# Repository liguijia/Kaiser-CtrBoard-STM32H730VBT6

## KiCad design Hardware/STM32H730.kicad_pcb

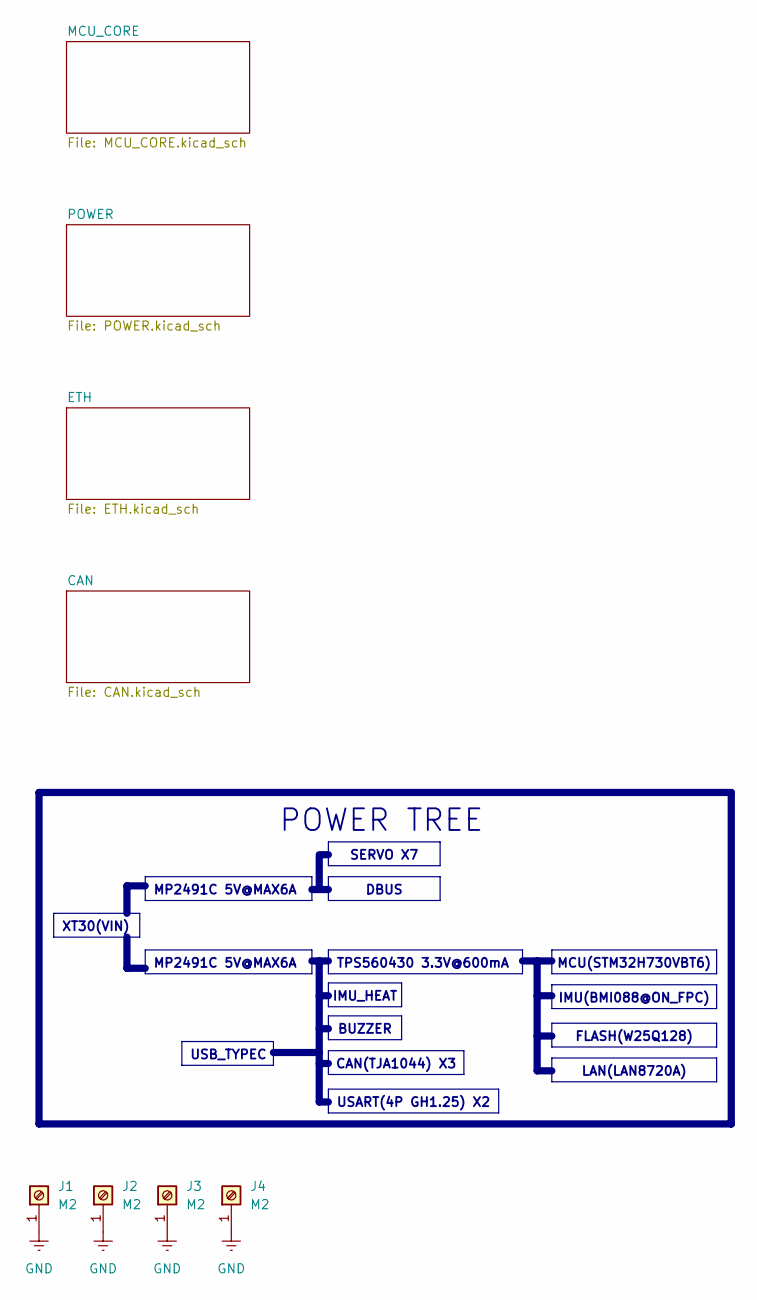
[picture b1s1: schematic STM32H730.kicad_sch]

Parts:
J1, J2, J3, J4: M2; MountingHole_2.2mm_M2_DIN965_Pad

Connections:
GND: J1.1, J2.1, J3.1, J4.1; also elsewhere on the board

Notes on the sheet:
LAN(LAN8720A)
SERVO X7
XT30(VIN)
FLASH(W25Q128)
MCU(STM32H730VBT6)
IMU(BMI088@ON_FPC)
DBUS
IMU_HEAT
CAN(TJA1044) X3
BUZZER
USART(4P GH1.25) X2
TPS560430 3.3V@600mA
MP2491C 5V@MAX6A
USB_TYPEC
POWER TREE

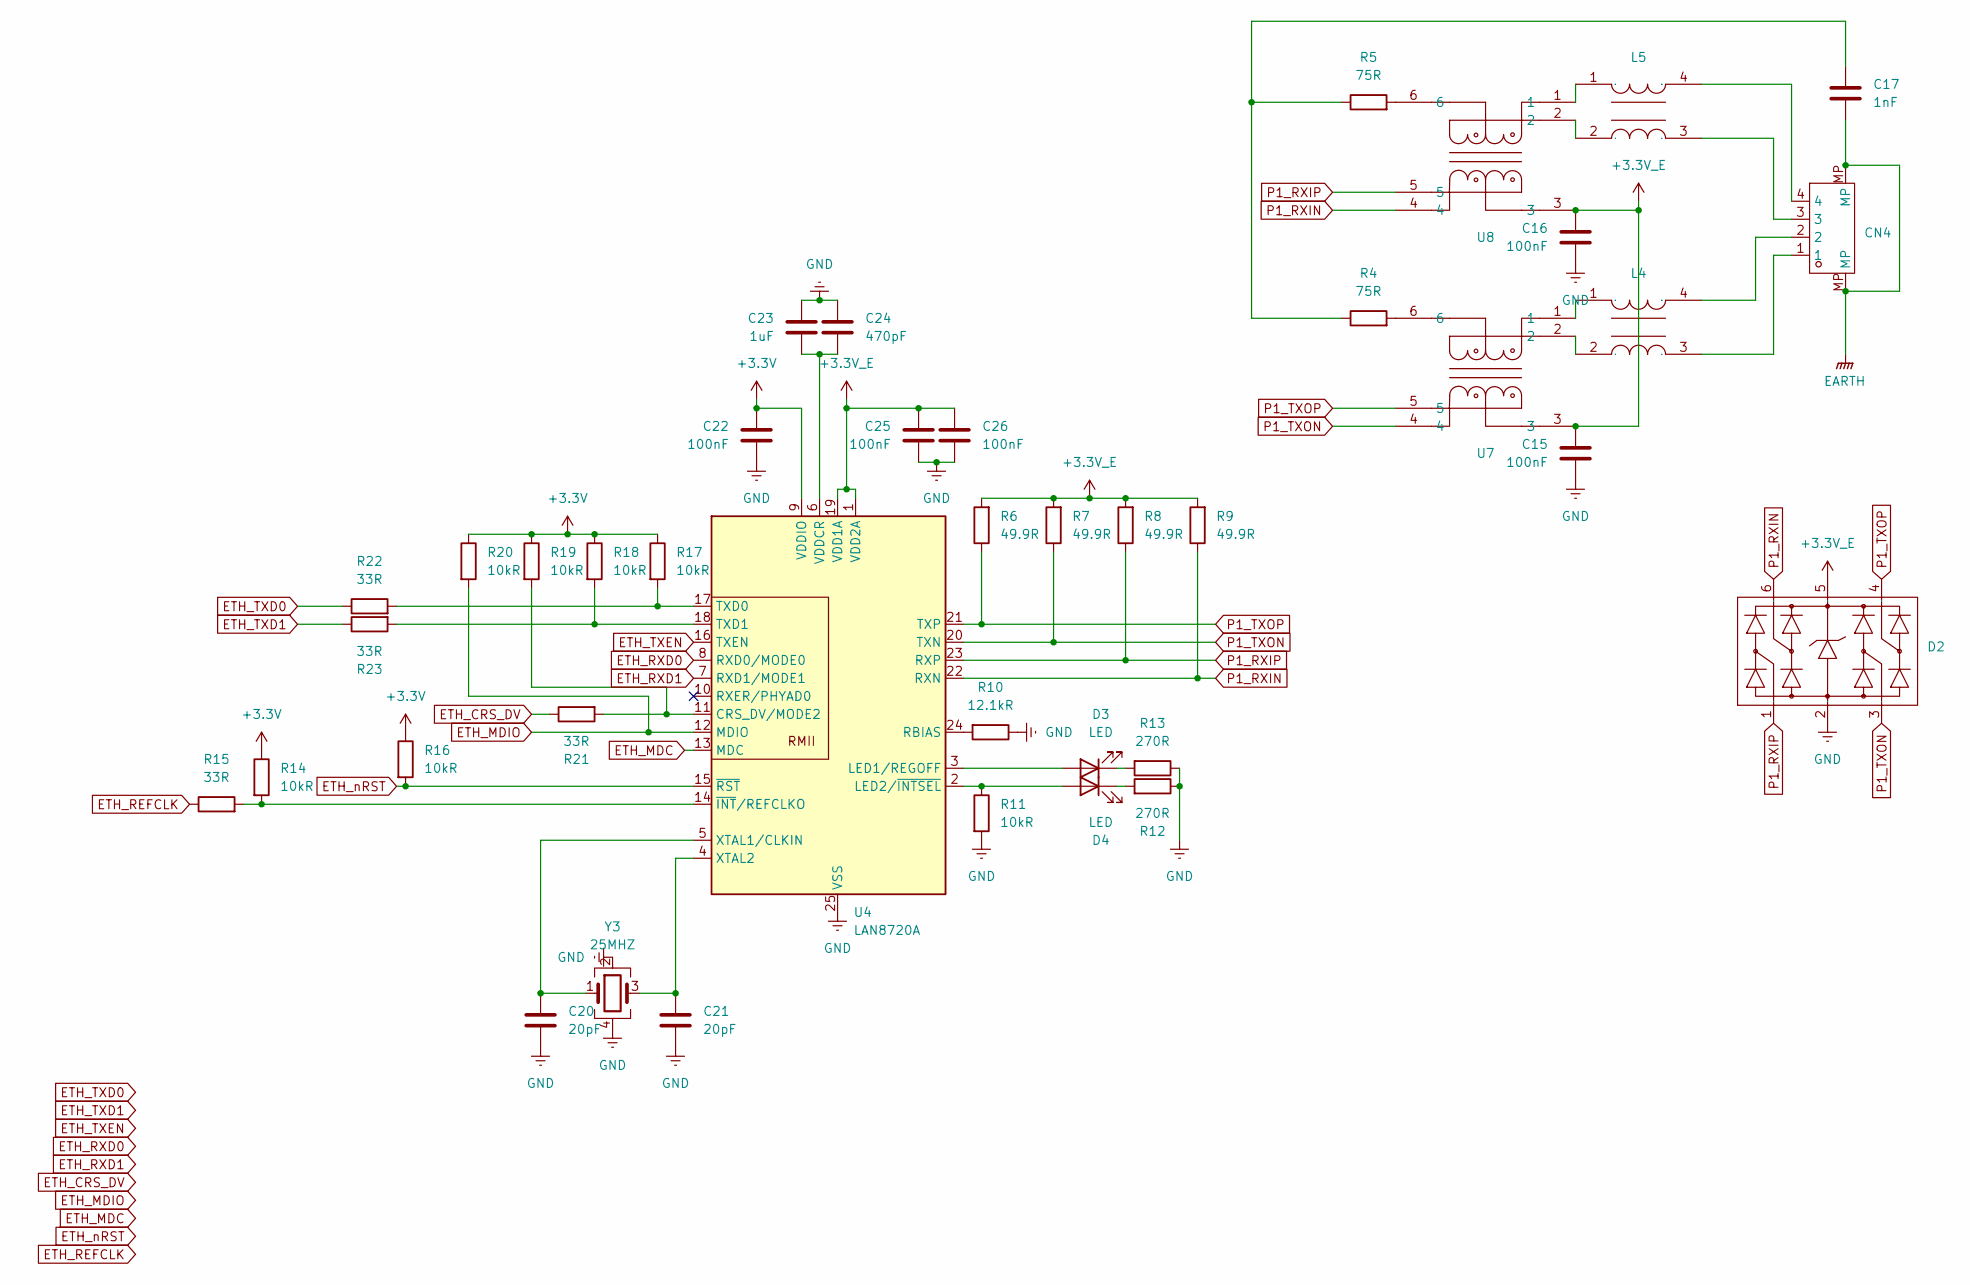
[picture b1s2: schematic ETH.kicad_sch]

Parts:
C15, C16, C22, C25, C26: 100nF; C_0402_1005Metric
C17: 1nF; C_0402_1005Metric
C20, C21: 20pF; C_0402_1005Metric
C23: 1uF; C_0402_1005Metric
C24: 470pF; C_0402_1005Metric
CN4: JST_GH_SM04B-GHS-TB_1x04-1MP_P1.25mm_Horizontal
D2: SOT-23-6_L2.9-W1.6-P0.95-LS2.8-BL
D3, D4: LED; LED_0402_1005Metric
L4, L5: IND-SMD_4P-L2.0-W1.2-TL
R4, R5: 75R; R_0402_1005Metric
R6, R7, R8, R9: 49.9R; R_0402_1005Metric
R10: 12.1kR; R_0402_1005Metric
R11, R14, R16, R17, R18, R19, R20: 10kR; R_0402_1005Metric
R12, R13: 270R; R_0402_1005Metric
R15, R21, R22, R23: 33R; R_0402_1005Metric
U4: LAN8720A; VQFN-24-1EP_4x4mm_P0.5mm_EP2.45x2.45mm_ThermalVias
U7, U8: FILTER-SMD_6P-L4.5-W3.2-P0.65
Y3: 25MHZ; Crystal_SMD_2520-4Pin_2.5x2.0mm

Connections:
+3.3V: C22.1, R14.1, R16.1, R17.1, R18.1, R19.1, R20.1, U4.9 (VDDIO); also elsewhere on the board
EARTH: C17.2, CN4.MP
ETH_CRS_DV: R21.1; also elsewhere on the board
ETH_MDC: U4.13 (MDC); also elsewhere on the board
ETH_MDIO: R20.2, U4.12 (MDIO); also elsewhere on the board
ETH_REFCLK: R15.1; also elsewhere on the board
ETH_RXD0: U4.8 (RXD0/MODE0); also elsewhere on the board
ETH_RXD1: U4.7 (RXD1/MODE1); also elsewhere on the board
ETH_TXD0: R22.1; also elsewhere on the board
ETH_TXD1: R23.1; also elsewhere on the board
ETH_TXEN: U4.16 (TXEN); also elsewhere on the board
ETH_nRST: R16.2, U4.15 (~RST); also elsewhere on the board
GND: C15.2, C16.2, C20.2, C21.2, C22.2, C23.2, C24.2, C25.2, C26.2, D2.2, R10.1, R11.2, R12.1, R13.1, U4.25 (VSS), Y3.2, Y3.4; also elsewhere on the board
unnamed: C17.1, R4.1, R5.1
unnamed: CN4.1, L4.3
unnamed: CN4.2, L4.4
unnamed: CN4.3, L5.3
unnamed: CN4.4, L5.4
unnamed: D3.2 (A), U4.3 (LED1/REGOFF)
unnamed: D3.1 (K), R13.2
unnamed: D4.2 (A), R11.1, U4.2 (LED2/~INTSEL)
unnamed: D4.1 (K), R12.2
unnamed: L4.1, U7.1
unnamed: L4.2, U7.2
unnamed: L5.1, U8.1
unnamed: L5.2, U8.2
unnamed: R4.2, U7.6
unnamed: R5.2, U8.6
unnamed: R19.2, R21.2, U4.11 (CRS_DV/MODE2)
unnamed: R10.2, U4.24 (RBIAS)
unnamed: R17.2, R22.2, U4.17 (TXD0)
unnamed: R18.2, R23.2, U4.18 (TXD1)
unnamed: C23.1, C24.1, U4.6 (VDDCR)
unnamed: C20.1, U4.5 (XTAL1/CLKIN), Y3.1
unnamed: C21.1, U4.4 (XTAL2), Y3.3
unnamed: R14.2, R15.2, U4.14 (~INT/REFCLKO)
P1_RXIN: D2.6, R9.1, U4.22 (RXN), U8.4
P1_RXIP: D2.1, R8.1, U4.23 (RXP), U8.5
P1_TXON: D2.3, R7.1, U4.20 (TXN), U7.4
P1_TXOP: D2.4, R6.1, U4.21 (TXP), U7.5

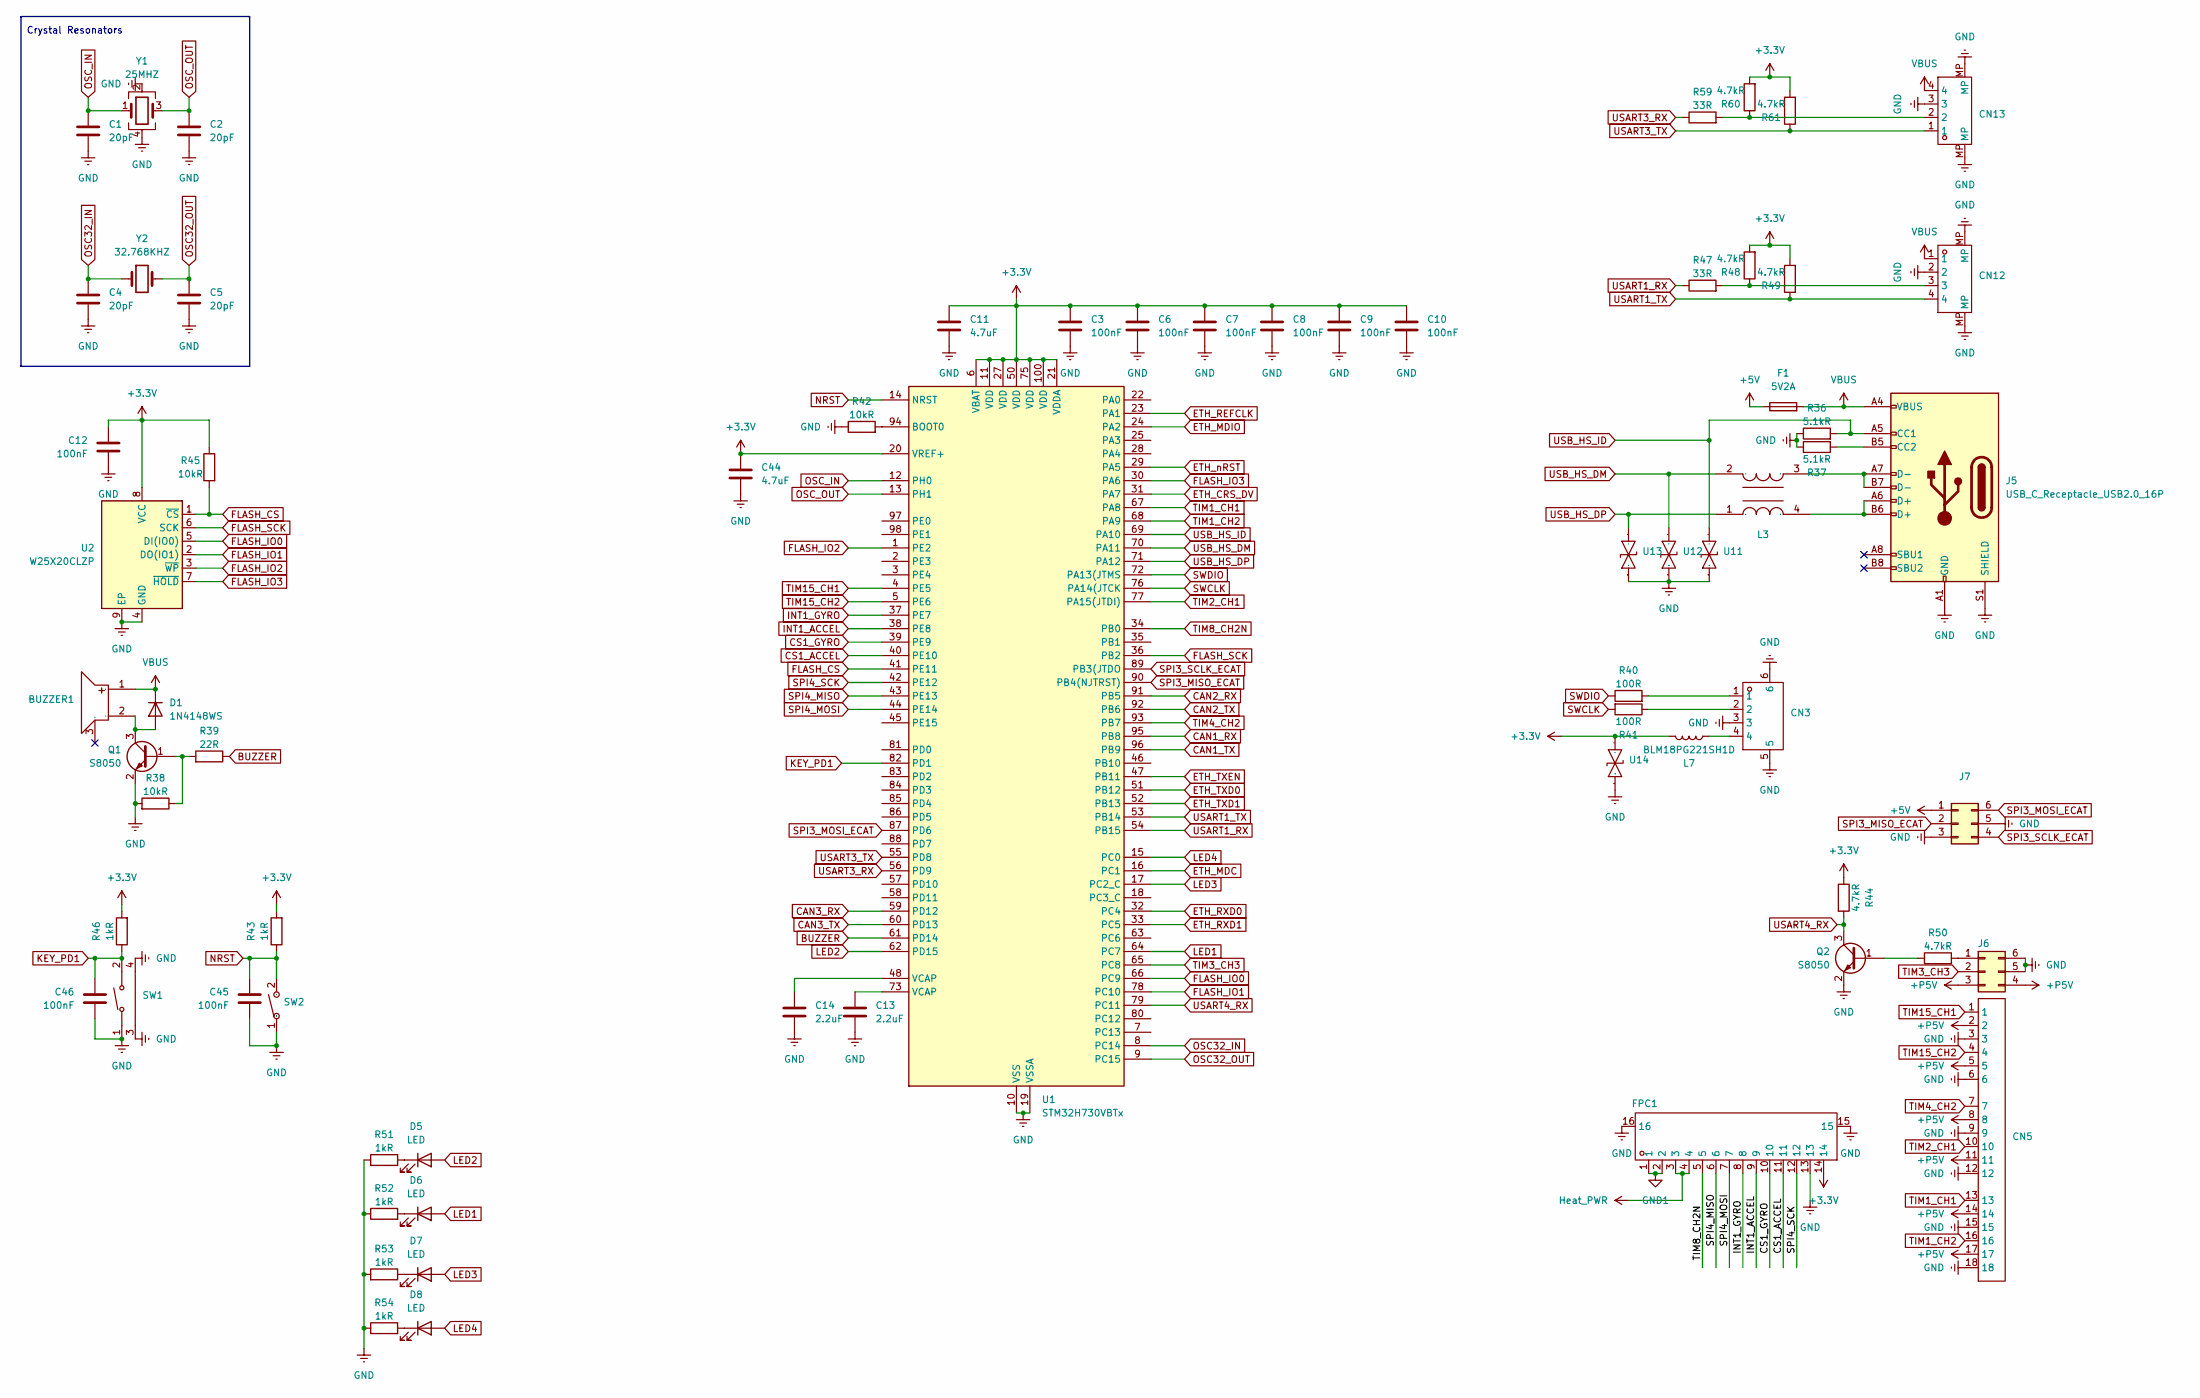
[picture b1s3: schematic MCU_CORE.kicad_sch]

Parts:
BUZZER1: BUZ-SMD_3P-L5.0-W5.0-BL
C1, C2, C4, C5: 20pF; C_0402_1005Metric
C3, C6, C7, C8, C9, C10, C12, C45, C46: 100nF; C_0402_1005Metric
C11, C44: 4.7uF; C_0402_1005Metric
C13, C14: 2.2uF; C_0402_1005Metric
CN3: CONN-SMD_4P-P1.25-MX1.25-4P-WT
CN5: HDR-TH_18P-P2.54-V-M-R3-C6-S5.08
CN12: JST_GH_SM04B-GHS-TB_1x04-1MP_P1.25mm_Horizontal
CN13: JST_GH_BM04B-GHS-TBT_1x04-1MP_P1.25mm_Vertical
D1: 1N4148WS; D_SOD-323
D5, D6, D7, D8: LED; LED_0603_1608Metric
F1: 5V2A; F0805
FPC1: FPC-SMD_14P-P0.50_XUNPU_FPC-05F-14PH15
J5: USB_C_Receptacle_USB2.0_16P; USB_C_Receptacle_GCT_USB4105-xx-A_16P_TopMnt_Horizontal
J6, J7: Conn_02x03_Counter_Clockwise; PinHeader_2x03_P2.54mm_Vertical
L3: IND-SMD_4P-L2.0-W1.2-TL
L7: BLM18PG221SH1D; L_0603_1608Metric
Q1, Q2: S8050; SOT-23
R36, R37: 5.1kR; R_0402_1005Metric
R38, R42, R45: 10kR; R_0402_1005Metric
R39: 22R; R_0402_1005Metric
R40: 100R; R_0603_1608Metric
R41: 100R; R_0402_1005Metric
R43, R46, R51, R52, R53, R54: 1kR; R_0402_1005Metric
R44, R48, R49, R50, R60, R61: 4.7kR; R_0402_1005Metric
R47, R59: 33R; R_0402_1005Metric
SW1: KEY-SMD_TX-1010-X-X
SW2: SW-SMD_L4.0-W3.0-LS4.8
U1: STM32H730VBTx; LQFP-100_14x14mm_P0.5mm
U2: W25X20CLZP; WSON-8-1EP_6x5mm_P1.27mm_EP3.4x4.3mm
U11, U12, U13, U14: SOD-882_L1.0-W0.6-BI
Y1: 25MHZ; Crystal_SMD_2520-4Pin_2.5x2.0mm
Y2: 32.768KHZ; Crystal_SMD_3215-2Pin_3.2x1.5mm

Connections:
+3.3V: C3.1, C6.1, C7.1, C8.1, C9.1, C10.1, C11.1, C12.1, C44.1, FPC1.14, L7.2, R43.2, R44.1, R45.1, R46.2, R48.2, R49.2, R60.2, R61.2, U1.6 (VBAT), U1.11 (VDD), U1.20 (VREF+), U1.21 (VDDA), U1.27 (VDD), U1.50 (VDD), U1.75 (VDD), U1.100 (VDD), U2.8 (VCC), U14.2; also elsewhere on the board
+5V: F1.1, J7.1; also elsewhere on the board
+P5V: CN5.2, CN5.5, CN5.8, CN5.11, CN5.14, CN5.17, J6.3, J6.4; also elsewhere on the board
BUZZER: R39.1, U1.61 (PD14)
CAN1_RX: U1.95 (PB8); also elsewhere on the board
CAN1_TX: U1.96 (PB9); also elsewhere on the board
CAN2_RX: U1.91 (PB5); also elsewhere on the board
CAN2_TX: U1.92 (PB6); also elsewhere on the board
CAN3_RX: U1.59 (PD12); also elsewhere on the board
CAN3_TX: U1.60 (PD13); also elsewhere on the board
CS1_ACCEL: FPC1.11, U1.40 (PE10)
CS1_GYRO: FPC1.10, U1.39 (PE9)
ETH_CRS_DV: U1.31 (PA7); also elsewhere on the board
ETH_MDC: U1.16 (PC1); also elsewhere on the board
ETH_MDIO: U1.24 (PA2); also elsewhere on the board
ETH_REFCLK: U1.23 (PA1); also elsewhere on the board
ETH_RXD0: U1.32 (PC4); also elsewhere on the board
ETH_RXD1: U1.33 (PC5); also elsewhere on the board
ETH_TXD0: U1.51 (PB12); also elsewhere on the board
ETH_TXD1: U1.52 (PB13); also elsewhere on the board
ETH_TXEN: U1.47 (PB11); also elsewhere on the board
ETH_nRST: U1.29 (PA5); also elsewhere on the board
FLASH_CS: R45.2, U1.41 (PE11), U2.1 (~CS)
FLASH_IO0: U1.66 (PC9), U2.5 (DI(IO0))
FLASH_IO1: U1.78 (PC10), U2.2 (DO(IO1))
FLASH_IO2: U1.1 (PE2), U2.3 (~WP)
FLASH_IO3: U1.30 (PA6), U2.7 (~HOLD)
FLASH_SCK: U1.36 (PB2), U2.6 (SCK)
GND: C1.2, C2.2, C3.2, C4.2, C5.2, C6.2, C7.2, C8.2, C9.2, C10.2, C11.2, C12.2, C13.2, C14.2, C44.2, C45.2, C46.2, CN3.3, CN3.5, CN3.6, CN5.3, CN5.6, CN5.9, CN5.12, CN5.15, CN5.18, CN12.2, CN12.MP, CN13.3, CN13.MP, FPC1.13, FPC1.15, FPC1.16, J5.A1 (GND), J5.A12 (GND), J5.B1 (GND), J5.B12 (GND), J5.S1 (SHIELD), J6.5, J6.6, J7.3, J7.5, Q1.2 (E), Q2.2 (E), R36.1, R37.1, R38.2, R42.1, R51.2, R52.1, R53.2, R54.1, SW1.1, SW1.3, SW1.4, SW2.1, U1.10 (VSS), U1.19 (VSSA), U1.26 (VSS), U1.49 (VSS), U1.74 (VSS), U1.99 (VSS), U2.4 (GND), U2.9 (EP), U11.1, U12.1, U13.1, U14.1, Y1.2, Y1.4; also elsewhere on the board
GND1: FPC1.1, FPC1.2; also elsewhere on the board
Heat_PWR: FPC1.3, FPC1.4; also elsewhere on the board
INT1_ACCEL: FPC1.9, U1.38 (PE8)
INT1_GYRO: FPC1.8, U1.37 (PE7)
KEY_PD1: C46.1, R46.1, SW1.2, U1.82 (PD1)
LED1: D6.2 (A), U1.64 (PC7)
LED2: D5.2 (A), U1.62 (PD15)
LED3: D7.2 (A), U1.17 (PC2_C)
LED4: D8.2 (A), U1.15 (PC0)
NRST: C45.1, R43.1, SW2.2, U1.14 (NRST)
unnamed: C13.1, U1.73 (VCAP)
unnamed: C14.1, U1.48 (VCAP)
unnamed: CN3.1, R40.2
unnamed: CN3.2, R41.1
unnamed: CN3.4, L7.1
unnamed: CN12.3, R47.2, R48.1
unnamed: CN13.2, R59.2, R60.1
unnamed: BUZZER1.2, D1.2 (A), Q1.3 (C)
unnamed: D5.1 (K), R51.1
unnamed: D6.1 (K), R52.2
unnamed: D7.1 (K), R53.1
unnamed: D8.1 (K), R54.2
unnamed: J5.B5 (CC2), R37.2
unnamed: J5.A6 (D+), J5.B6 (D+), L3.4
unnamed: J5.A7 (D-), J5.B7 (D-), L3.3
unnamed: J6.1, R50.2
unnamed: Q1.1 (B), R38.1, R39.2
unnamed: Q2.1 (B), R50.1
unnamed: R42.2, U1.94 (BOOT0)
OSC32_IN: C4.1, U1.8 (PC14), Y2.1
OSC32_OUT: C5.1, U1.9 (PC15), Y2.2
OSC_IN: C1.1, U1.12 (PH0), Y1.1
OSC_OUT: C2.1, U1.13 (PH1), Y1.3
SPI3_MISO_ECAT: J7.2, U1.90 (PB4(NJTRST))
SPI3_MOSI_ECAT: J7.6, U1.87 (PD6)
SPI3_SCLK_ECAT: J7.4, U1.89 (PB3(JTDO)
SPI4_MISO: FPC1.6, U1.43 (PE13)
SPI4_MOSI: FPC1.7, U1.44 (PE14)
SPI4_SCK: FPC1.12, U1.42 (PE12)
SWCLK: R41.2, U1.76 (PA14(JTCK)
SWDIO: R40.1, U1.72 (PA13(JTMS)
TIM1_CH1: CN5.13, U1.67 (PA8)
TIM1_CH2: CN5.16, U1.68 (PA9)
TIM2_CH1: CN5.10, U1.77 (PA15(JTDI))
TIM3_CH3: J6.2, U1.65 (PC8)
TIM4_CH2: CN5.7, U1.93 (PB7)
TIM8_CH2N: FPC1.5, U1.34 (PB0)
TIM15_CH1: CN5.1, U1.4 (PE5)
TIM15_CH2: CN5.4, U1.5 (PE6)
USART1_RX: R47.1, U1.54 (PB15)
USART1_TX: CN12.4, R49.1, U1.53 (PB14)
USART3_RX: R59.1, U1.56 (PD9)
USART3_TX: CN13.1, R61.1, U1.55 (PD8)
USART4_RX: Q2.3 (C), R44.2, U1.79 (PC11)
USB_HS_DM: L3.2, U1.70 (PA11), U12.2
USB_HS_DP: L3.1, U1.71 (PA12), U13.2
USB_HS_ID: J5.A5 (CC1), R36.2, U1.69 (PA10), U11.2
VBUS: BUZZER1.1, CN12.1, CN13.4, D1.1 (K), F1.2, J5.A4 (VBUS), J5.A9 (VBUS), J5.B4 (VBUS), J5.B9 (VBUS)

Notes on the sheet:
Crystal Resonators

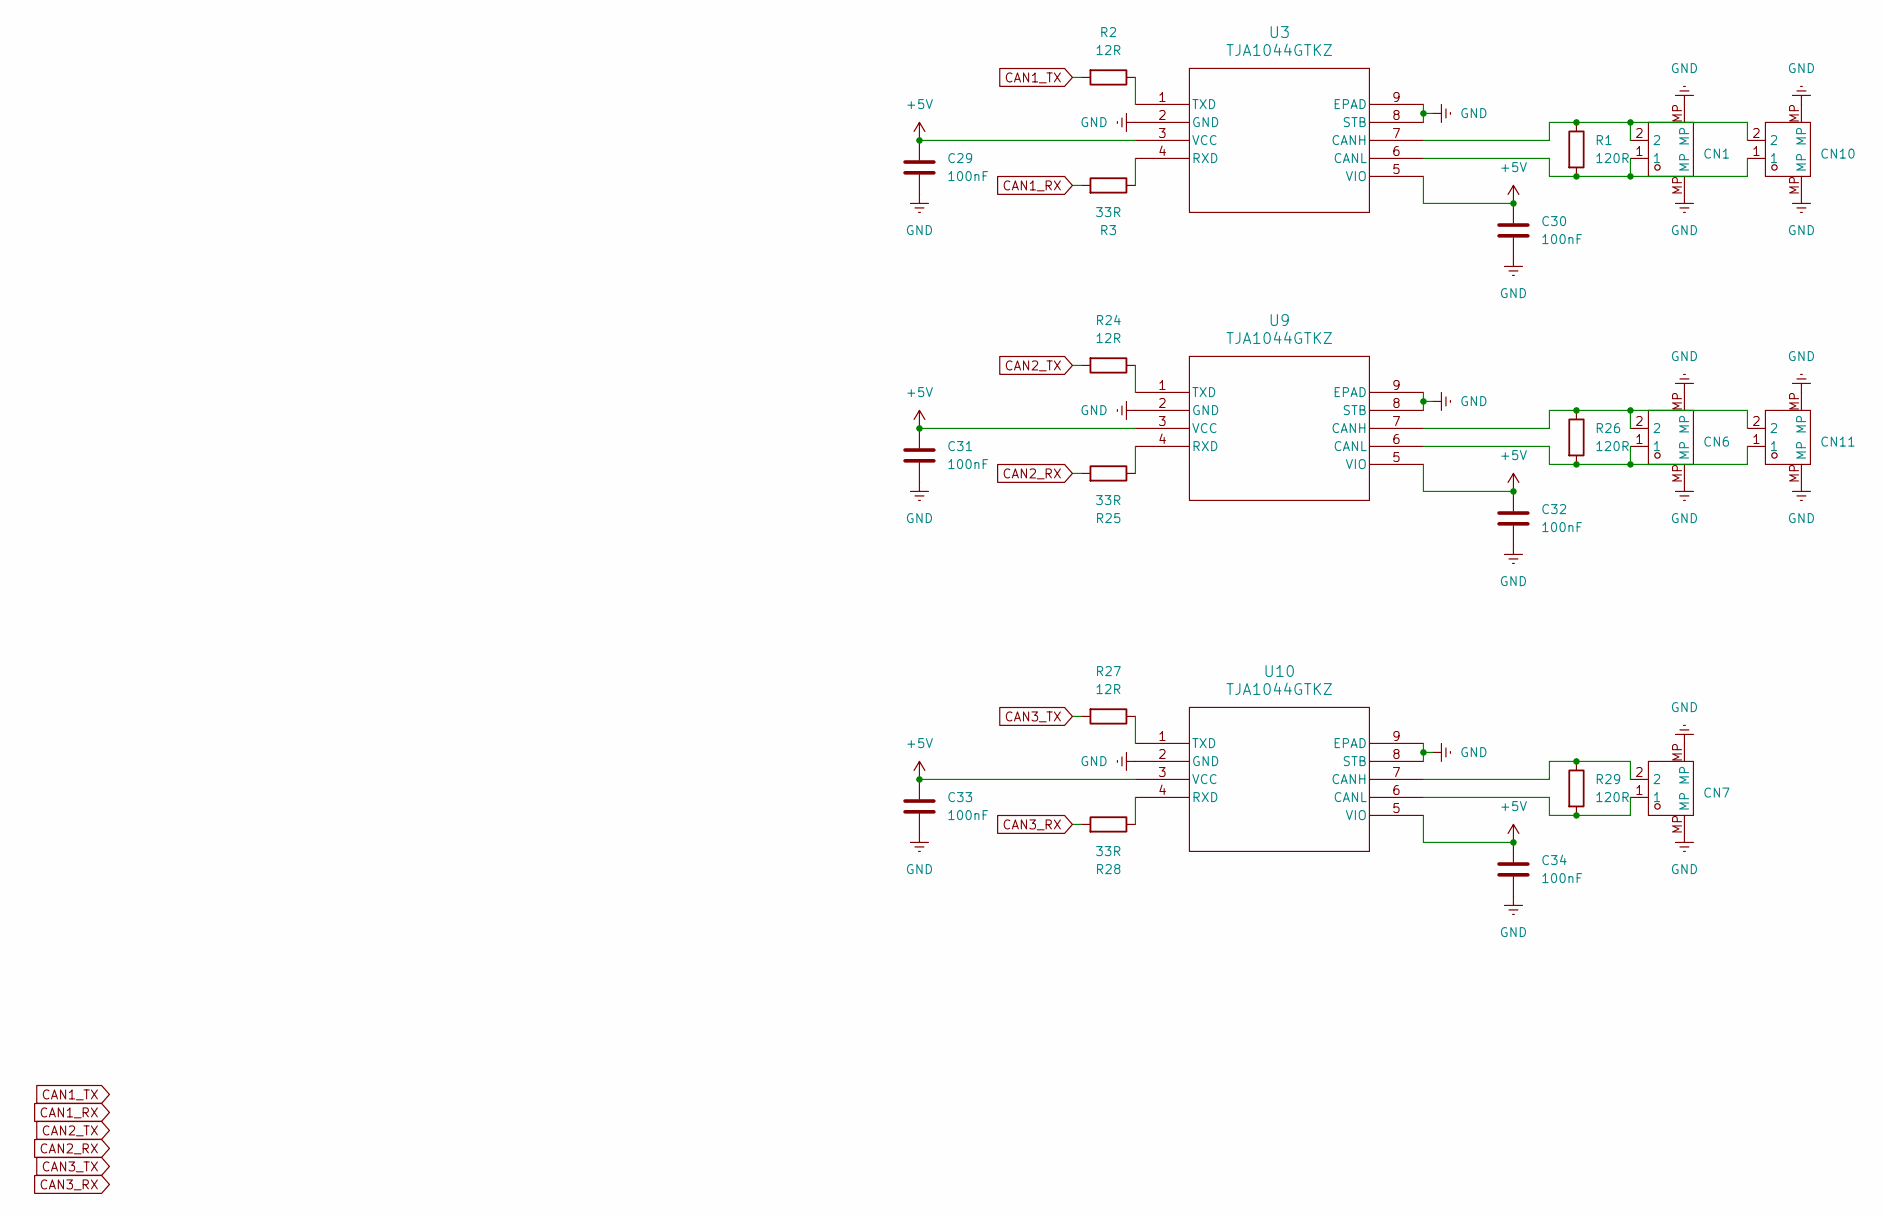
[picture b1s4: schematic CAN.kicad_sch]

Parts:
C29, C30, C31, C32, C33, C34: 100nF; C_0402_1005Metric
CN1, CN6, CN7, CN10, CN11: JST_GH_SM02B-GHS-TB_1x02-1MP_P1.25mm_Horizontal
R1, R26, R29: 120R; R_0402_1005Metric
R2, R24, R27: 12R; R_0402_1005Metric
R3, R25, R28: 33R; R_0402_1005Metric
U3, U9, U10: TJA1044GTKZ; HVSON8_SOT782-1_NXP

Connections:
+5V: C29.1, C30.1, C31.1, C32.1, C33.1, C34.1, U3.3 (VCC), U3.5 (VIO), U9.3 (VCC), U9.5 (VIO), U10.3 (VCC), U10.5 (VIO); also elsewhere on the board
CAN1_RX: R3.2; also elsewhere on the board
CAN1_TX: R2.2; also elsewhere on the board
CAN2_RX: R25.2; also elsewhere on the board
CAN2_TX: R24.2; also elsewhere on the board
CAN3_RX: R28.2; also elsewhere on the board
CAN3_TX: R27.2; also elsewhere on the board
GND: C29.2, C30.2, C31.2, C32.2, C33.2, C34.2, CN1.MP, CN6.MP, CN7.MP, CN10.MP, CN11.MP, U3.2 (GND), U3.8 (STB), U3.9 (EPAD), U9.2 (GND), U9.8 (STB), U9.9 (EPAD), U10.2 (GND), U10.8 (STB), U10.9 (EPAD); also elsewhere on the board
unnamed: CN1.2, CN10.2, R1.1, U3.7 (CANH)
unnamed: CN1.1, CN10.1, R1.2, U3.6 (CANL)
unnamed: R3.1, U3.4 (RXD)
unnamed: R2.1, U3.1 (TXD)
unnamed: CN6.2, CN11.2, R26.1, U9.7 (CANH)
unnamed: CN6.1, CN11.1, R26.2, U9.6 (CANL)
unnamed: R25.1, U9.4 (RXD)
unnamed: R24.1, U9.1 (TXD)
unnamed: CN7.2, R29.1, U10.7 (CANH)
unnamed: CN7.1, R29.2, U10.6 (CANL)
unnamed: R28.1, U10.4 (RXD)
unnamed: R27.1, U10.1 (TXD)

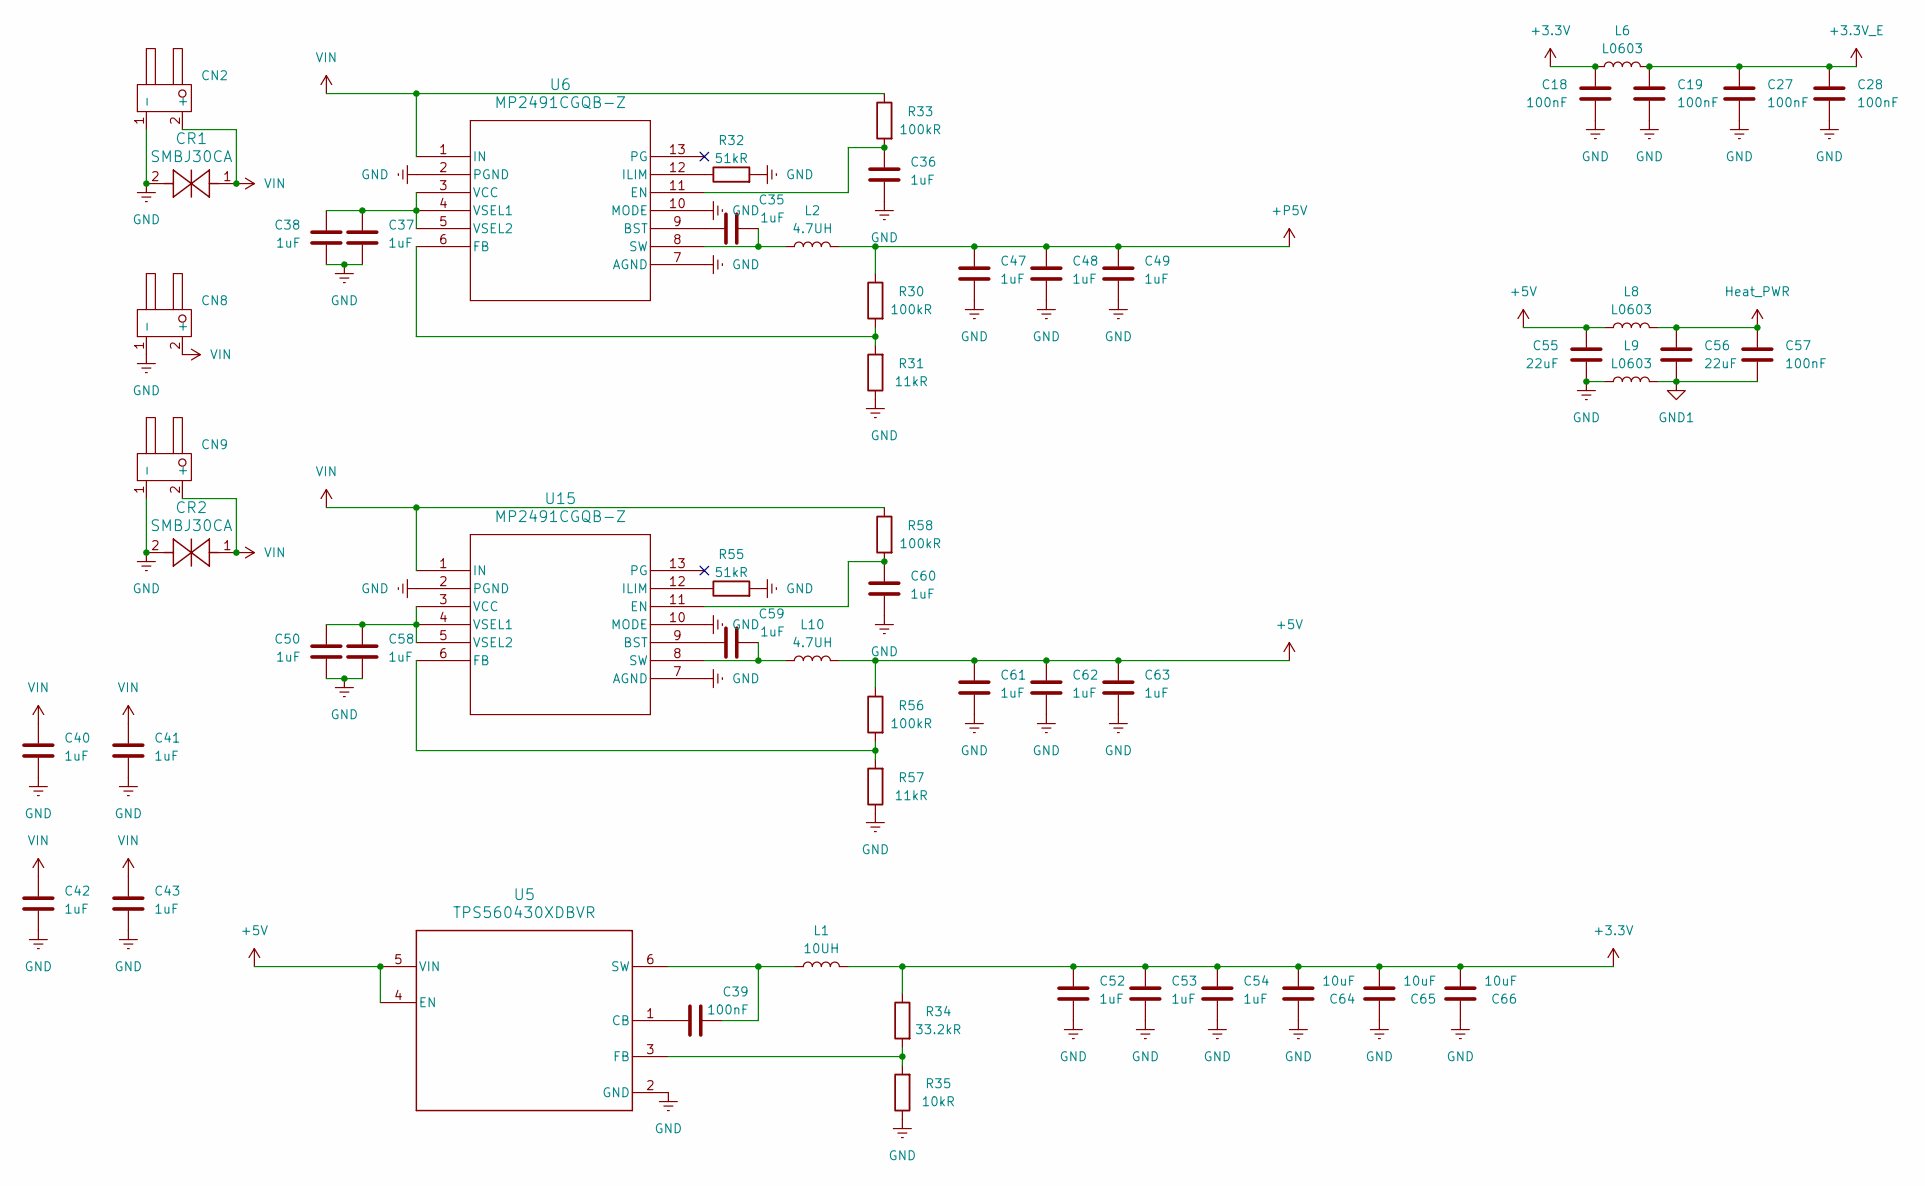
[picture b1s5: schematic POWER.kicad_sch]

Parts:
C18, C19, C27, C28, C39, C57: 100nF; C_0402_1005Metric
C35, C36, C37, C38, C50, C58, C59, C60: 1uF; C_0402_1005Metric
C40, C41, C42, C43, C47, C48, C49, C52, C53, C54, C61, C62, C63: 1uF; C_1206_3216Metric
C55, C56: 22uF; C_0402_1005Metric
C64, C65, C66: 10uF; C_0402_1005Metric
CN2, CN8, CN9: AMASS_XT30U-M_1x02_P5.0mm_Vertical
CR1, CR2: SMBJ30CA; DO-214AA_LTF
L1: 10UH; IND-SMD_L2.5-W2.0
L2, L10: 4.7UH; L_Chilisin_BMRA00040420
L6, L8, L9: L0603
R30, R33, R56, R58: 100kR; R_0402_1005Metric
R31, R57: 11kR; R_0402_1005Metric
R32, R55: 51kR; R_0402_1005Metric
R34: 33.2kR; R_0402_1005Metric
R35: 10kR; R_0402_1005Metric
U5: TPS560430XDBVR; SOT-23-6
U6, U15: MP2491CGQB-Z; QFN-13_2p5MMx3MM_MNP

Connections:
+3.3V: C18.1, C52.2, C53.2, C54.2, C64.2, C65.2, C66.2, L1.2, L6.1, R34.1; also elsewhere on the board
+5V: C55.1, C61.2, C62.2, C63.2, L8.1, L10.2, R56.1, U5.4 (EN), U5.5 (VIN); also elsewhere on the board
+P5V: C47.2, C48.2, C49.2, L2.2, R30.1; also elsewhere on the board
GND: C18.2, C19.2, C27.2, C28.2, C36.1, C37.1, C38.1, C40.1, C41.1, C42.1, C43.1, C47.1, C48.1, C49.1, C50.1, C52.1, C53.1, C54.1, C55.2, C58.1, C60.1, C61.1, C62.1, C63.1, C64.1, C65.1, C66.1, CN2.1 (-), CN8.1 (-), CN9.1 (-), CR1.2, CR2.2, L9.1, R31.1, R32.2, R35.1, R55.2, R57.1, U5.2 (GND), U6.2 (PGND), U6.7 (AGND), U6.10 (MODE), U15.2 (PGND), U15.7 (AGND), U15.10 (MODE); also elsewhere on the board
GND1: C56.2, C57.2, L9.2; also elsewhere on the board
Heat_PWR: C56.1, C57.1, L8.2; also elsewhere on the board
unnamed: C39.1, U5.1 (CB)
unnamed: R34.2, R35.2, U5.3 (FB)
unnamed: C39.2, L1.1, U5.6 (SW)
unnamed: C35.1, U6.9 (BST)
unnamed: C36.2, R33.2, U6.11 (EN)
unnamed: R30.2, R31.2, U6.6 (FB)
unnamed: R32.1, U6.12 (ILIM)
unnamed: C35.2, L2.1, U6.8 (SW)
unnamed: C37.2, C38.2, U6.3 (VCC), U6.4 (VSEL1), U6.5 (VSEL2)
unnamed: C59.1, U15.9 (BST)
unnamed: C60.2, R58.2, U15.11 (EN)
unnamed: R56.2, R57.2, U15.6 (FB)
unnamed: R55.1, U15.12 (ILIM)
unnamed: C59.2, L10.1, U15.8 (SW)
unnamed: C50.2, C58.2, U15.3 (VCC), U15.4 (VSEL1), U15.5 (VSEL2)
VIN: C40.2, C41.2, C42.2, C43.2, CN2.2 (+), CN8.2 (+), CN9.2 (+), CR1.1, CR2.1, R33.1, R58.1, U6.1 (IN), U15.1 (IN)

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
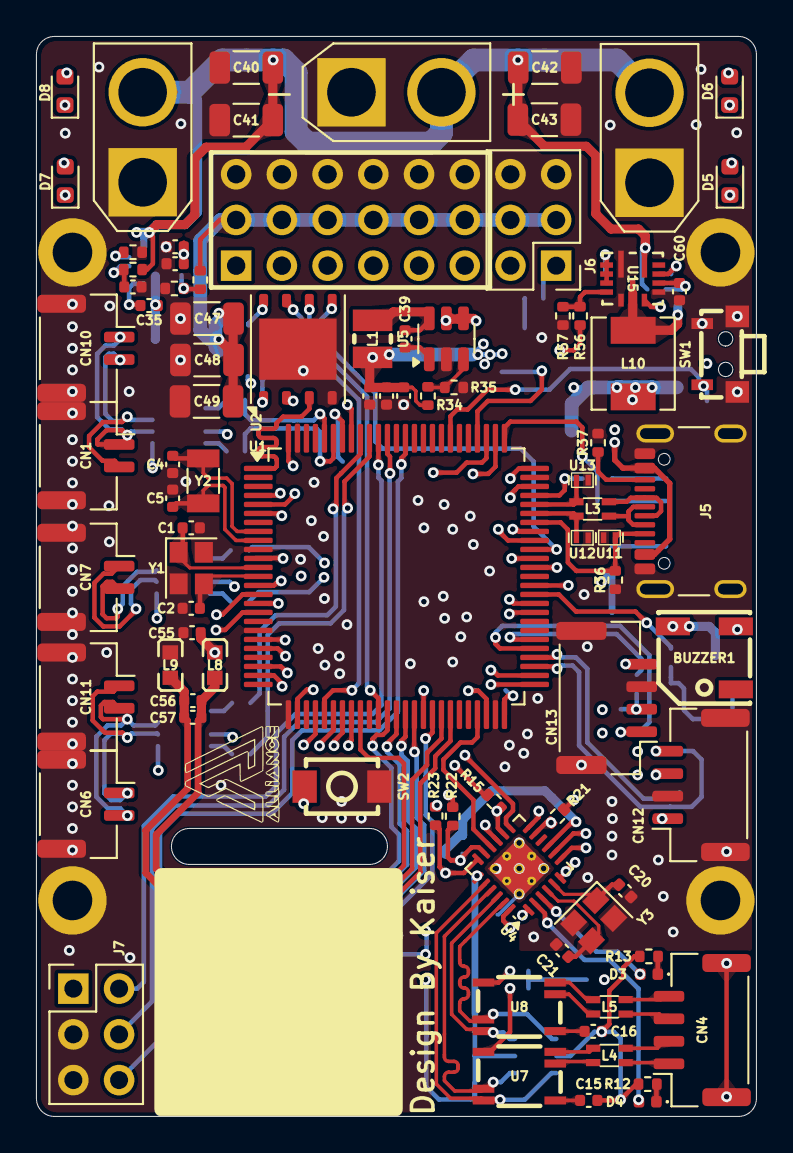
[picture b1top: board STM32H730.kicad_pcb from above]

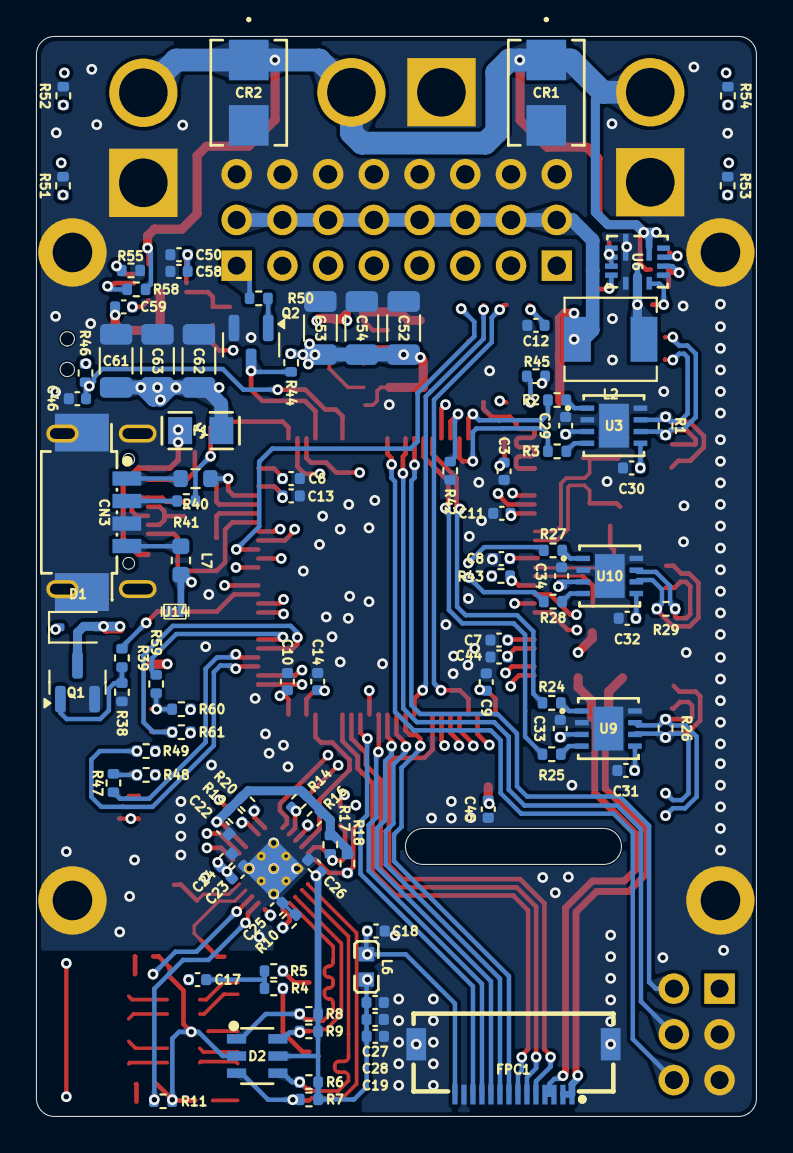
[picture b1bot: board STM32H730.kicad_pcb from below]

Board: 4 copper layers, 40.0 x 60.0 mm, 191 parts (100 on the bottom side), 146 nets.

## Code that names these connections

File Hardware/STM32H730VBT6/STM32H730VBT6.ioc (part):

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Mcu.Name=STM32H730VBTx
Mcu.Package=LQFP100
Mcu.UserName=STM32H730VBTx
PA0.Mode=Asynchronous
PA0.Signal=UART4_TX
PA1.Mode=RMII
PA1.Signal=ETH_REF_CLK
PA10.Mode=OTG/Dual-Role-Device-FS
PA10.Signal=USB_OTG_HS_ID
PA11.Mode=OTG/Dual-Role-Device-FS
PA11.Signal=USB_OTG_HS_DM
PA12.Mode=OTG/Dual-Role-Device-FS
PA12.Signal=USB_OTG_HS_DP
PA13(JTMS/SWDIO).Mode=Serial_Wire
PA13(JTMS/SWDIO).Signal=DEBUG_JTMS-SWDIO
PA14(JTCK/SWCLK).Mode=Serial_Wire
PA14(JTCK/SWCLK).Signal=DEBUG_JTCK-SWCLK
PA15(JTDI).Signal=S_TIM2_CH1_ETR
PA2.Mode=RMII
PA2.Signal=ETH_MDIO
PA6.Mode=OCTOSPI1_IOL_Port1L
PA6.Signal=OCTOSPIM_P1_IO3
PA7.Mode=RMII
PA7.Signal=ETH_CRS_DV
PA8.Signal=S_TIM1_CH1
PA9.Signal=S_TIM1_CH2
PB0.GPIOParameters=GPIO_Label
PB0.GPIO_Label=IMU_HEAT_PWM
PB0.Signal=TIM8_CH2N
PB11.Mode=RMII
PB11.Signal=ETH_TX_EN
PB12.Mode=RMII
PB12.Signal=ETH_TXD0
PB13.Mode=RMII
PB13.Signal=ETH_TXD1
PB14.Signal=USART1_TX
PB15.Signal=USART1_RX
PB2.Mode=O1_P1_CLK
PB2.Signal=OCTOSPIM_P1_CLK
PB3(JTDO/TRACESWO).Mode=Full_Duplex_Master
PB3(JTDO/TRACESWO).Signal=SPI3_SCK
PB4(NJTRST).Mode=Full_Duplex_Master
PB4(NJTRST).Signal=SPI3_MISO
PB5.Mode=FDCAN_Activate
PB5.Signal=FDCAN2_RX
PB6.Mode=FDCAN_Activate
PB6.Signal=FDCAN2_TX
PB7.Signal=S_TIM4_CH2
PB8.Mode=FDCAN_Activate
PB8.Signal=FDCAN1_RX
PB9.Mode=FDCAN_Activate
PB9.Signal=FDCAN1_TX
PC0.GPIOParameters=GPIO_Label
PC0.GPIO_Label=LED4
PC0.Signal=GPIO_Output
PC1.Mode=RMII
PC1.Signal=ETH_MDC
PC10.Mode=OCTOSPI1_IOL_Port1L
PC10.Signal=OCTOSPIM_P1_IO1
PC11.Mode=Asynchronous
PC11.Signal=UART4_RX
PC14-OSC32_IN.Mode=LSE-External-Oscillator
PC14-OSC32_IN.Signal=RCC_OSC32_IN
PC15-OSC32_OUT.Mode=LSE-External-Oscillator
PC15-OSC32_OUT.Signal=RCC_OSC32_OUT
PC2_C.GPIOParameters=GPIO_Label
PC2_C.GPIO_Label=LED3
PC2_C.Signal=GPIO_Output
PC4.Mode=RMII
PC4.Signal=ETH_RXD0
PC5.Mode=RMII
PC5.Signal=ETH_RXD1
PC7.GPIOParameters=GPIO_Label
PC7.GPIO_Label=LED1
PC7.Signal=GPIO_Output
PC8.Signal=S_TIM3_CH3
PC9.Mode=OCTOSPI1_IOL_Port1L
PC9.Signal=OCTOSPIM_P1_IO0
PD12.Mode=FDCAN_Activate
PD12.Signal=FDCAN3_RX
PD13.Mode=FDCAN_Activate
PD13.Signal=FDCAN3_TX
PD14.GPIOParameters=GPIO_Label
PD14.GPIO_Label=BUZZER
PD14.Signal=S_TIM4_CH3
PD15.GPIOParameters=GPIO_Label
PD15.GPIO_Label=LED2
PD15.Signal=GPIO_Output
PD6.Mode=Full_Duplex_Master
PD6.Signal=SPI3_MOSI
PE10.GPIOParameters=GPIO_Label
PE10.GPIO_Label=IMU_CS1_ACCEL
PE10.Signal=GPIO_Output
PE11.Mode=OCTOSPI1_Port1_NCS
PE11.Signal=OCTOSPIM_P1_NCS
PE12.GPIOParameters=GPIO_Label
PE12.GPIO_Label=IMU_SPI4_SCK
PE12.Mode=Full_Duplex_Master
PE12.Signal=SPI4_SCK
PE13.GPIOParameters=GPIO_Label
PE13.GPIO_Label=IMU_SPI4_MISO
PE13.Mode=Full_Duplex_Master
PE13.Signal=SPI4_MISO
PE14.GPIOParameters=GPIO_Label
PE14.GPIO_Label=IMU_SPI4_MOSI
PE14.Mode=Full_Duplex_Master
PE14.Signal=SPI4_MOSI
PE2.Mode=OCTOSPI1_IOL_Port1L
PE2.Signal=OCTOSPIM_P1_IO2
PE5.Signal=S_TIM15_CH1
PE6.Signal=S_TIM15_CH2
PE7.GPIOParameters=GPIO_Label
PE7.GPIO_Label=IMU_INT1_GYRO
PE7.Signal=GPIO_Output
PE8.GPIOParameters=GPIO_Label
PE8.GPIO_Label=IMU_INT1_ACCEL
PE8.Signal=GPIO_Output
PE9.GPIOParameters=GPIO_Label
PE9.GPIO_Label=IMU_CS1_GYRO
PE9.Signal=GPIO_Output
PH0-OSC_IN.Mode=HSE-External-Oscillator
PH0-OSC_IN.Signal=RCC_OSC_IN
PH1-OSC_OUT.Mode=HSE-External-Oscillator
PH1-OSC_OUT.Signal=RCC_OSC_OUT
RCC.SYSCLKFreq_VALUE=550000000
RCC.SYSCLKSource=RCC_SYSCLKSOURCE_PLLCLK
board=custom

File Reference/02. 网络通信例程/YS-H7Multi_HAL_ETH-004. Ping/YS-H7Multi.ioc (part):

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Mcu.Name=STM32H743IITx
Mcu.Package=LQFP176
Mcu.UserName=STM32H743IITx
PA1.Mode=RMII
PA1.Signal=ETH_REF_CLK
PA13.Mode=Serial_Wire
PA13.Signal=SYS_JTMS-SWDIO
PA14.Mode=Serial_Wire
PA14.Signal=SYS_JTCK-SWCLK
PA2.Mode=RMII
PA2.Signal=ETH_MDIO
PA7.Mode=RMII
PA7.Signal=ETH_CRS_DV
PB10.Mode=Asynchronous
PB10.Signal=USART3_TX
PB11.Mode=Asynchronous
PB11.Signal=USART3_RX
PB12.Mode=RMII
PB12.Signal=ETH_TXD0
PB13.Mode=RMII
PB13.Signal=ETH_TXD1
PC1.Mode=RMII
PC1.Signal=ETH_MDC
PC4.Mode=RMII
PC4.Signal=ETH_RXD0
PC5.Mode=RMII
PC5.Signal=ETH_RXD1
PE5.Signal=GPIO_Output
PF13.Signal=GPIO_Output
PG11.Mode=RMII
PG11.Signal=ETH_TX_EN
PH0-OSC_IN.Mode=HSE-External-Oscillator
PH0-OSC_IN.Signal=RCC_OSC_IN
PH1-OSC_OUT.Mode=HSE-External-Oscillator
PH1-OSC_OUT.Signal=RCC_OSC_OUT
PH9.Signal=GPIO_Input
RCC.SYSCLKFreq_VALUE=400000000
RCC.SYSCLKSource=RCC_SYSCLKSOURCE_PLLCLK
board=custom

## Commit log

2024-11-15 usb_cdc
2024-11-15 add IMU&DBUS
2024-11-17 fix can，but imu overheat still exsit
2024-11-17 Trying ETH
2024-11-21 add some reference，but eth still not work
